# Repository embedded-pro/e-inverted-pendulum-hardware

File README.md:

# e-inverted-pendulum — Hardware

Hardware for the [e-inverted-pendulum](https://github.com/embedded-pro/e-inverted-pendulum) two-wheeled self-balancing
robot. The PCB is the robot's chassis: one vertical 85 × 130 mm 4-layer board carries the electronics, the battery and
the motor bracket. Built and assembled at JLCPCB.

This repository holds the **KiCad** design, the Python scripts that generate the schematic and sync the board, and the
ngspice simulation suite. The firmware lives in its own repository and is the source of the requirements.

> **Status: Phase 3 (layout), placement handed to the owner (D-032).** Phases 0–2 (requirements, schematic,
> simulation) are signed off. The schematic is complete, simulated and ERC-clean; the board has its outline, rule
> areas and bracket holes, with every part in the staging area. See [docs/plan.md](docs/plan.md) for the phase gates.

---

## Highlights

- **STM32WB55RGV6** with BLE 5. The whole RF corner is a copy of ST's NUCLEO-WB55 (MB1355 rev D-01, D-037): internal
  SMPS, 32 MHz HSE without external caps, `MLPF-WB55-01E3` → 3.6 nH / 1.2 pF match → printed meander antenna on
  ST's ground-free tab at the top-left corner (PCB antenna only, D-038). The MCU decoupling sits on top at the
  Nucleo's spots, or the nearest free spot to each pin (DS11929 Fig. 16 values, D-038).
- **DRV8711 gate driver with four external half-bridges** (`CSD88537ND`) for two MG310 gear motors: indexer bypassed
  (PWMMODE 1), 50 mΩ low-side shunts with Kelvin taps, 2.0 A trip, SS34 clamps on every phase node. The power stage is
  a copy of TI's BOOST-DRV8711 (D-040, `docs/drive.md`).
- **Battery path:** XT30, 4 A fuse, back-to-back `AO4805` P-FETs for reverse polarity and switching, with a simulated
  Miller soft start; `SMBJ15A` after the FETs.
- **Rails:** `TPS62933F` buck to 5 V (encoders, RGB LEDs, LDO), `TLV75533P` LDO to 3.3 V, ferrite-filtered VDDA.
- **12 RGB LEDs** (`WS2812B-2020-V6`) on one PA7 timer/DMA pin through a 5 V `SN74AHCT1G125`: it is also a toy (D-035).
  No buttons, no buzzer.
- **Test pads** on every sheet (rails, motor phases and shunts, PWM, SPI, encoders, IMU, I2C), net names on the silk.
- **Sensors and storage:** `MPU-6500` IMU on SPI2, `W25Q16JV` flash on SPI1, `M24C64` EEPROM and an `M24SR64-Y` NFC tag
  with a printed 13.56 MHz coil on I2C3, plus a Qwiic port.
- **Encoder inputs:** ESD at the connector, 100 Ω + 1 nF, `SN74LVC3G17` Schmitt buffers with 5 V-tolerant inputs.

---

## Board architecture

The schematic has 8 hierarchical sheets, one functional block each, drawn as titled boxes with design notes (the
e-psu-hardware pattern, D-033):

| Sheet | Function | Key parts |
|-------|----------|-----------|
| `e-inverted-pendulum.kicad_sch` | Root: sheet descriptions, power flow, grounding | — |
| `power_entry` | Battery input, fuse, power switch with soft start, TVS, VBAT sense | `AO4805`, `SMBJ15A`, XT30 |
| `logic_power` | 5V0 buck and 3V3 LDO | `TPS62933F`, `TLV75533P` |
| `mcu` | MCU pin map, decoupling, SMPS, clocks, reset/boot, STDC14 debug | `STM32WB55RGV6` |
| `rf` | 2.4 GHz path and printed antenna | `MLPF-WB55-01E3` |
| `drive` | Gate driver, four half-bridges, current sense | `DRV8711`, `CSD88537ND` |
| `motors_encoders` | Motor + encoder connectors, encoder conditioning | JST PH 6-pin, `TPD4E05U06`, `SN74LVC3G17` |
| `imu_flash` | IMU and SPI flash | `MPU-6500`, `W25Q16JV` |
| `ui` | Status LED, 12 RGB LEDs, Qwiic, EEPROM, NFC tag | `WS2812B-2020-V6`, `SN74AHCT1G125`, `M24C64`, `M24SR64-Y` |

---

## Design requirements

The firmware is the requirement source. [docs/requirements.md](docs/requirements.md) traces every hardware
requirement to a firmware `REQ-*` ID or to a decision in [docs/decisions.md](docs/decisions.md). The key targets:

| Item | Target | Source |
|------|--------|--------|
| Battery | 3S LiPo, 9.0–12.6 V, XT30, reverse-polarity protected | D-011, D-021 |
| Motors | 2 × MG310 1:20 (7.4 V), average motor voltage capped at 7.4 V by firmware | D-027 |
| Drive | DRV8711, PWMMODE 1, trip 2.0 A (ISGAIN 20, TORQUE 186), 0.5 A continuous by firmware I²t | D-027, S0 |
| Encoders | Hall A/B, no index; 1040 counts per wheel revolution (13 PPR is an assumption) | D-028 |
| Radio | BLE on the STM32WB55, RF corner copied from ST's NUCLEO-WB55 (MB1355) | D-001, D-007, D-037 |
| PCB | 85 × 130 mm, 4 layers JLC04161H-7628, L2 solid GND, JLCPCB assembly | D-008, D-024 |

[docs/firmware-interface.md](docs/firmware-interface.md) lists the settings the firmware must apply (DRV8711 registers,
voltage cap, ADC scaling, clock trims, I2C addresses).

### Simulation

`python3 simulation/run_all.py` runs S0–S5 (motor sizing, power entry, H-bridge switching, bus ripple, rails, ADC and
encoder edges). Two power-entry failures and one phase-node abs-max violation were found and fixed in the schematic.
Details: [simulation/REPORT.md](simulation/REPORT.md).

---

## Repository layout

```
e-inverted-pendulum-hardware/
├── hardware/
│   └── e-inverted-pendulum/          # KiCad 10 project
│       ├── e-inverted-pendulum.kicad_pro / .kicad_sch (root) / .kicad_pcb / .kicad_dru
│       ├── power_entry / logic_power / mcu / rf / drive / motors_encoders / imu_flash / ui .kicad_sch
│       ├── e-inverted-pendulum.kicad_sym    # project symbols
│       ├── e-inverted-pendulum.pretty/      # project footprints (XT30, STDC14, MB1355_* and MB1163_* from ST, ...)
│       └── sym-lib-table, fp-lib-table
├── scripts/
│   ├── schgen/                       # schematic generator: design/*.py -> hardware/ (D-020, D-033)
│   ├── pcb/                          # board sync (add-only, D-032), RF / NFC corner pastes (rf_block.py D-037, nfc_block.py D-039), renders
│   ├── export_review.py              # review package     -> review_exports/<board>/
│   ├── export_jlcpcb.py              # fab + assembly     -> manufacturing/<board>/
│   ├── export_release.py             # release bundle     -> release/<board>-<version>.zip
│   ├── visual_diff.py                # PR visual diff     -> diff/<board>/
│   ├── rf_reference.py               # ST MB1355 files (reference/, gitignored) -> pcb/mb1355_rf.json + MB1355_* footprints
│   ├── nfc_reference.py              # ST MB1163 Gerbers (reference/, gitignored) -> pcb/mb1163_nfc.json + MB1163_* footprints
│   └── check_*.py, design_calcs.py, nfc_coil.py, gcpw.py, export_bom.py, jlc_stock.py
├── simulation/                       # ngspice suite (S0–S5) + REPORT.md
├── pin-data/                         # pin map and the DS11929 package data it is checked against
├── bom/                              # part catalogue, BOM, stock check
├── docs/
│   ├── plan.md, requirements.md, decisions.md, design-calcs.md, power-map.md, rf.md, nfc.md, layout.md, ...
│   ├── robot-hardware-design-guide.md    # design and review knowledge base
│   ├── schematic.pdf
│   └── images/                       # board renders
├── .claude/agents/pendulum-board-reviewer.md   # design-review agent
├── PROJECT_CONTEXT.md                # design summary, decisions, open items
└── .github/workflows/                # hardware checks, kicad-bot, visual diff, release
```

Generated outputs are gitignored: `review_exports/`, `manufacturing/`, `release/`, `diff/`.

---

## Getting started

KiCad 10 project. Open `hardware/e-inverted-pendulum/e-inverted-pendulum.kicad_pro`.

```bash
git clone https://github.com/embedded-pro/e-inverted-pendulum-hardware.git
```

### Headless checks (the same ones CI runs)

```bash
python3 scripts/check_pinmap.py --firmware ../e-inverted-pendulum
```

```bash
python3 scripts/schgen/build.py
```

```bash
python3 scripts/schgen/check.py
```

```bash
kicad-cli sch erc --severity-all --exit-code-violations hardware/e-inverted-pendulum/e-inverted-pendulum.kicad_sch
```

```bash
python3 scripts/check_netlist.py && python3 scripts/check_library.py
```

### Changing the schematic

The schematic is generated: edit `scripts/schgen/design/<sheet>.py`, then rebuild. `scripts/schgen/render.sh` rebuilds,
checks the netlist against `expected.json`, writes `docs/schematic.pdf` and renders each sheet to PNG. After a
drawing-only change, prove the circuit is unchanged against the last commit:

```bash
python3 scripts/schgen/check_equivalence.py HEAD
```

Then bring the board in line (new parts land in the staging area; nothing on the board moves):

```bash
python3 scripts/pcb/board.py --rules <path to pcb_rules.py from the pcb-design-rules skill>
```

The RF corner is a copy of ST's NUCLEO-WB55 (MB1355 rev D-01, D-037). It is pasted once, and a second
run does nothing (since D-046 it is no longer a group and has no pours; `docs/rf.md`):

```bash
python3 scripts/pcb/rf_block.py --apply
```

`scripts/rf_reference.py` re-derives `scripts/pcb/mb1355_rf.json` and the `MB1355_*` footprints from ST's files, which are
kept out of the repository in `reference/mb1355/` (ST's Open Platform License).

The NFC corner is a copy of ST's X-NUCLEO-NFC01A1 (MB1163 rev C-01, D-039): the M24SR64-Y, its ANT14 coil, tuning caps,
copper and pour, pasted the same way (`docs/nfc.md`). `scripts/nfc_reference.py` re-derives `scripts/pcb/mb1163_nfc.json`
and the `MB1163_*` footprints from ST's Gerbers in `reference/mb1163/`; `scripts/nfc_coil.py` checks the coil.

```bash
python3 scripts/pcb/nfc_block.py --apply
```

### Review and fabrication packages

- The export, BOM, stock, datasheet and visual-diff scripts are thin wrappers around the hardware-design plugin's,
  pinned in `scripts/plugin.py`; `python3 scripts/plugin_gates.py` runs the plugin's gates as CI does (D-064).
- `python3 scripts/export_review.py`: ERC/DRC, netlist, BOM, PDFs and renders for a design review, used by the
  `pendulum-board-reviewer` agent in [`.claude/agents/`](.claude/agents/).
- `python3 scripts/export_jlcpcb.py`: Gerbers, drill, BOM and CPL for JLCPCB.
- `python3 scripts/export_bom.py` then `python3 scripts/jlc_stock.py bom/bom.csv --boards 5`: BOM and live stock.

---

## Before ordering

1. Finish Phase 3: placement (owner), routing, DRC clean with schematic parity, the `power-pcb-layout` §7 and
   `rf-layout` §12 checklists ([docs/plan.md](docs/plan.md)).
2. Re-run the stock check; every line must be in stock for the order quantity.
3. JLCPCB options (PCB + assembly, D-036): 4 layers, JLC04161H-7628, 1.6 mm, 1 oz outer / 0.5 oz inner; impedance
   control only if JLCPCB holds MB1355's RF line as drawn (0.6 / 0.2 mm on L1 over L3, `docs/rf.md`). Check every CPL rotation in the preview
   (the WS2812B-2020 footprint is the datasheet pattern turned 180°).
4. Leave the DNP parts off: antenna-match C401, shield clips SC401–SC404, NFC tuning spares C821–C823 and pull-ups R805 / R806, sense filters C501/C504, motor
   snubbers C603/C607, encoder pull-ups, R602.

---

## Continuous integration

- [`hardware.yml`](.github/workflows/hardware.yml): pin map, regenerate the schematic with no diff, netlist against
  the generator's intent, ERC, netlist and symbol/footprint checks.
- [`kicad-bot.yml`](.github/workflows/kicad-bot.yml): [kicad-bot](https://github.com/embedded-pro/kicad-bot) ERC/DRC
  with schematic parity, on pushes to `main` and on pull requests; DRC does not fail the build until the board is
  routed. kicad-bot runs without KiCad's libraries, so its ERC shows library-lookup warnings; `hardware.yml` is the
  library check.
- [`kicad-diff.yml`](.github/workflows/kicad-diff.yml): red/green visual diff of schematic and board on pull requests.
- KiCad on GitHub runners: `scripts/install_kicad.sh 10` (and kicad-bot ≥ v0.1.5) pins the KiCad PPA to `amd64`.
  Ubuntu 26.04 runners otherwise install Ubuntu's KiCad 9, which can't open this project; the script fails if
  `kicad-cli` isn't 10.x.
- [`release.yml`](.github/workflows/release.yml): [release-please](https://github.com/googleapis/release-please) from
  Conventional Commits; each release attaches the fabrication bundle from `scripts/export_release.py`.

Third-party actions are pinned to a full commit SHA. CI is a guardrail, not a design review: use the
`pendulum-board-reviewer` agent with [docs/robot-hardware-design-guide.md](docs/robot-hardware-design-guide.md) for that.

Design rules come from the `hardware-design` skills in
[claude-hardware-skills](https://github.com/gabrielfrasantos/claude-hardware-skills).

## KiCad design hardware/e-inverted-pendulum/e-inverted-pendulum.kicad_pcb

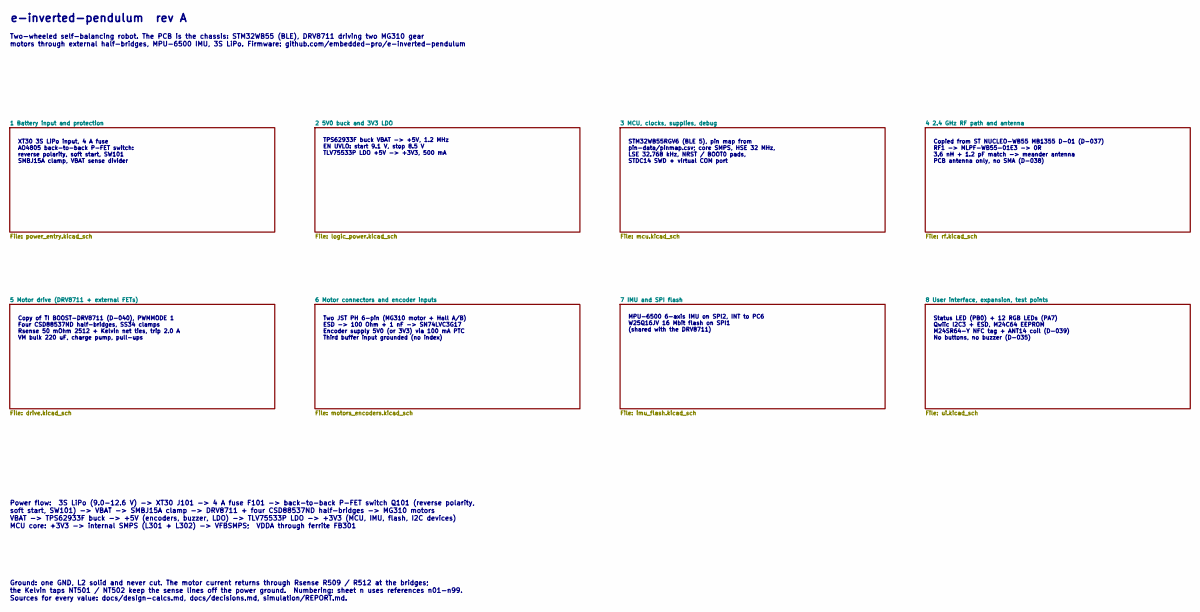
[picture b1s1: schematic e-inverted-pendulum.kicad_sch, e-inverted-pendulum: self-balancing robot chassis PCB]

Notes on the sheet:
Two JST PH 6-pin (MG310 motor + Hall A/B) ESD -> 100 Ohm + 1 nF -> SN74LVC3G17 Encoder supply 5V0 (or 3V3) via 100 mA PTC Third buffer input grounded (no index)
Copy of TI BOOST-DRV8711 (D-040), PWMMODE 1 Four CSD88537ND half-bridges, SS34 clamps Rsense 50 mOhm 2512 + Kelvin net ties, trip 2.0 A VM bulk 220 uF, charge pump, pull-ups
Copied from ST NUCLEO-WB55 MB1355 D-01 (D-037) RF1 -> MLPF-WB55-01E3 -> 0R 3.6 nH + 1.2 pF match -> meander antenna PCB antenna only, no SMA (D-038)
MPU-6500 6-axis IMU on SPI2, INT to PC6 W25Q16JV 16 Mbit flash on SPI1 (shared with the DRV8711)
Status LED (PB0) + 12 RGB LEDs (PA7) Qwiic I2C3 + ESD, M24C64 EEPROM M24SR64-Y NFC tag + ANT14 coil (D-039) No buttons, no buzzer (D-035)
Two-wheeled self-balancing robot. The PCB is the chassis: STM32WB55 (BLE), DRV8711 driving two MG310 gear motors through external half-bridges, MPU-6500 IMU, 3S LiPo. Firmware: github.com/embedded-pro/e-inverted-pendulum
XT30 3S LiPo input, 4 A fuse AO4805 back-to-back P-FET switch: reverse polarity, soft start, SW101 SMBJ15A clamp, VBAT sense divider
e-inverted-pendulum rev A
TPS62933F buck VBAT -> +5V, 1.2 MHz EN UVLO: start 9.1 V, stop 8.5 V TLV75533P LDO +5V -> +3V3, 500 mA
Ground: one GND, L2 solid and never cut. The motor current returns through Rsense R509 / R512 at the bridges; the Kelvin taps NT501 / NT502 keep the sense lines off the power ground. Numbering: sheet n uses references n01-n99. Sources for every value: docs/design-calcs.md, docs/decisions.md, simula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
STM32WB55RGV6 (BLE 5), pin map from pin-data/pinmap.csv; core SMPS, HSE 32 MHz, LSE 32.768 kHz, NRST / BOOT0 pads, STDC14 SWD + virtual COM port
Power flow: 3S LiPo (9.0-12.6 V) -> XT30 J101 -> 4 A fuse F101 -> back-to-back P-FET switch Q101 (reverse polarity, soft start, SW101) -> VBAT -> SMBJ15A clamp -> DRV8711 + four CSD88537ND half-bridges -> MG310 motors VBAT -> TPS62933F buck -> +5V (encoders, buzzer, LDO) -> TLV75533P LDO -> +3V3 (M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

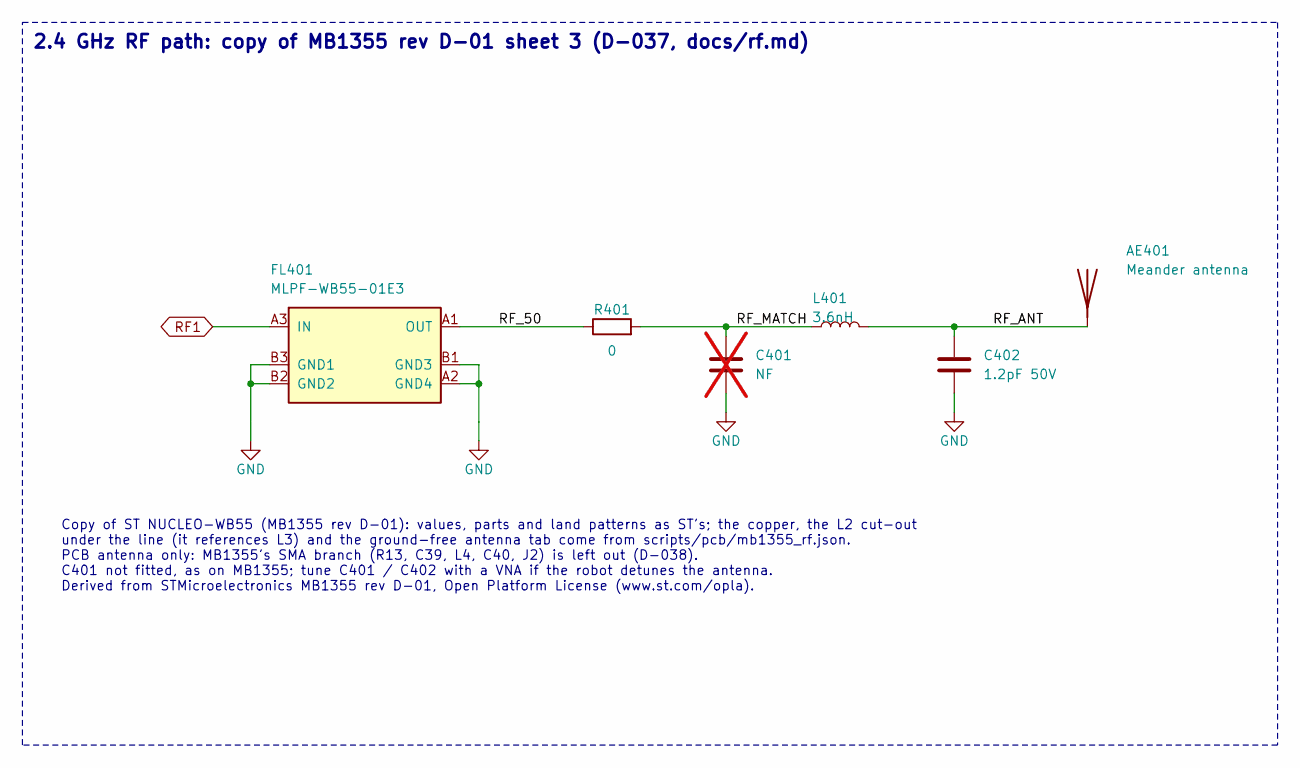
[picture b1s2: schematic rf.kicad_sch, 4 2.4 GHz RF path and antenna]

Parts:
AE401: Meander antenna; MB1355_Meander_Antenna
C401: NF; MB1355_0402_CAP_NPOL; not fitted
C402: 1.2pF 50V; MB1355_0402_CAP_NPOL; MPN GJM1555C1H1R2WB01D; LCSC C76899
FL401: MLPF-WB55-01E3; MB1355_ST_CSP650x58P2x3_160x100x42; MPN MLPF-WB55-01E3; LCSC C2651048
L401: 3.6nH; MB1355_0402_COIL; MPN LQG15HS3N6S02D; LCSC C19216
R401: 0; MB1355_0402_RES; MPN 0402WGF0000TCE; LCSC C17168

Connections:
/4 2.4 GHz RF path and antenna/RF_50: FL401.A1 (OUT), R401.1
/4 2.4 GHz RF path and antenna/RF_ANT: AE401.1, C402.1, L401.2
/4 2.4 GHz RF path and antenna/RF_MATCH: C401.1, L401.1, R401.2
GND: C401.2, C402.2, FL401.A2 (GND4), FL401.B1 (GND3), FL401.B2 (GND2), FL401.B3 (GND1); also elsewhere on the board
RF1: FL401.A3 (IN); also elsewhere on the board

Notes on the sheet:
2.4 GHz RF path: copy of MB1355 rev D-01 sheet 3 (D-037, docs/rf.md)
Copy of ST NUCLEO-WB55 (MB1355 rev D-01): values, parts and land patterns as ST's; the copper, the L2 cut-out under the line (it references L3) and the ground-free antenna tab come from scripts/pcb/mb1355_rf.json. PCB antenna only: MB1355's SMA branch (R13, C39, L4, C40, J2) is left out (D-038). C4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

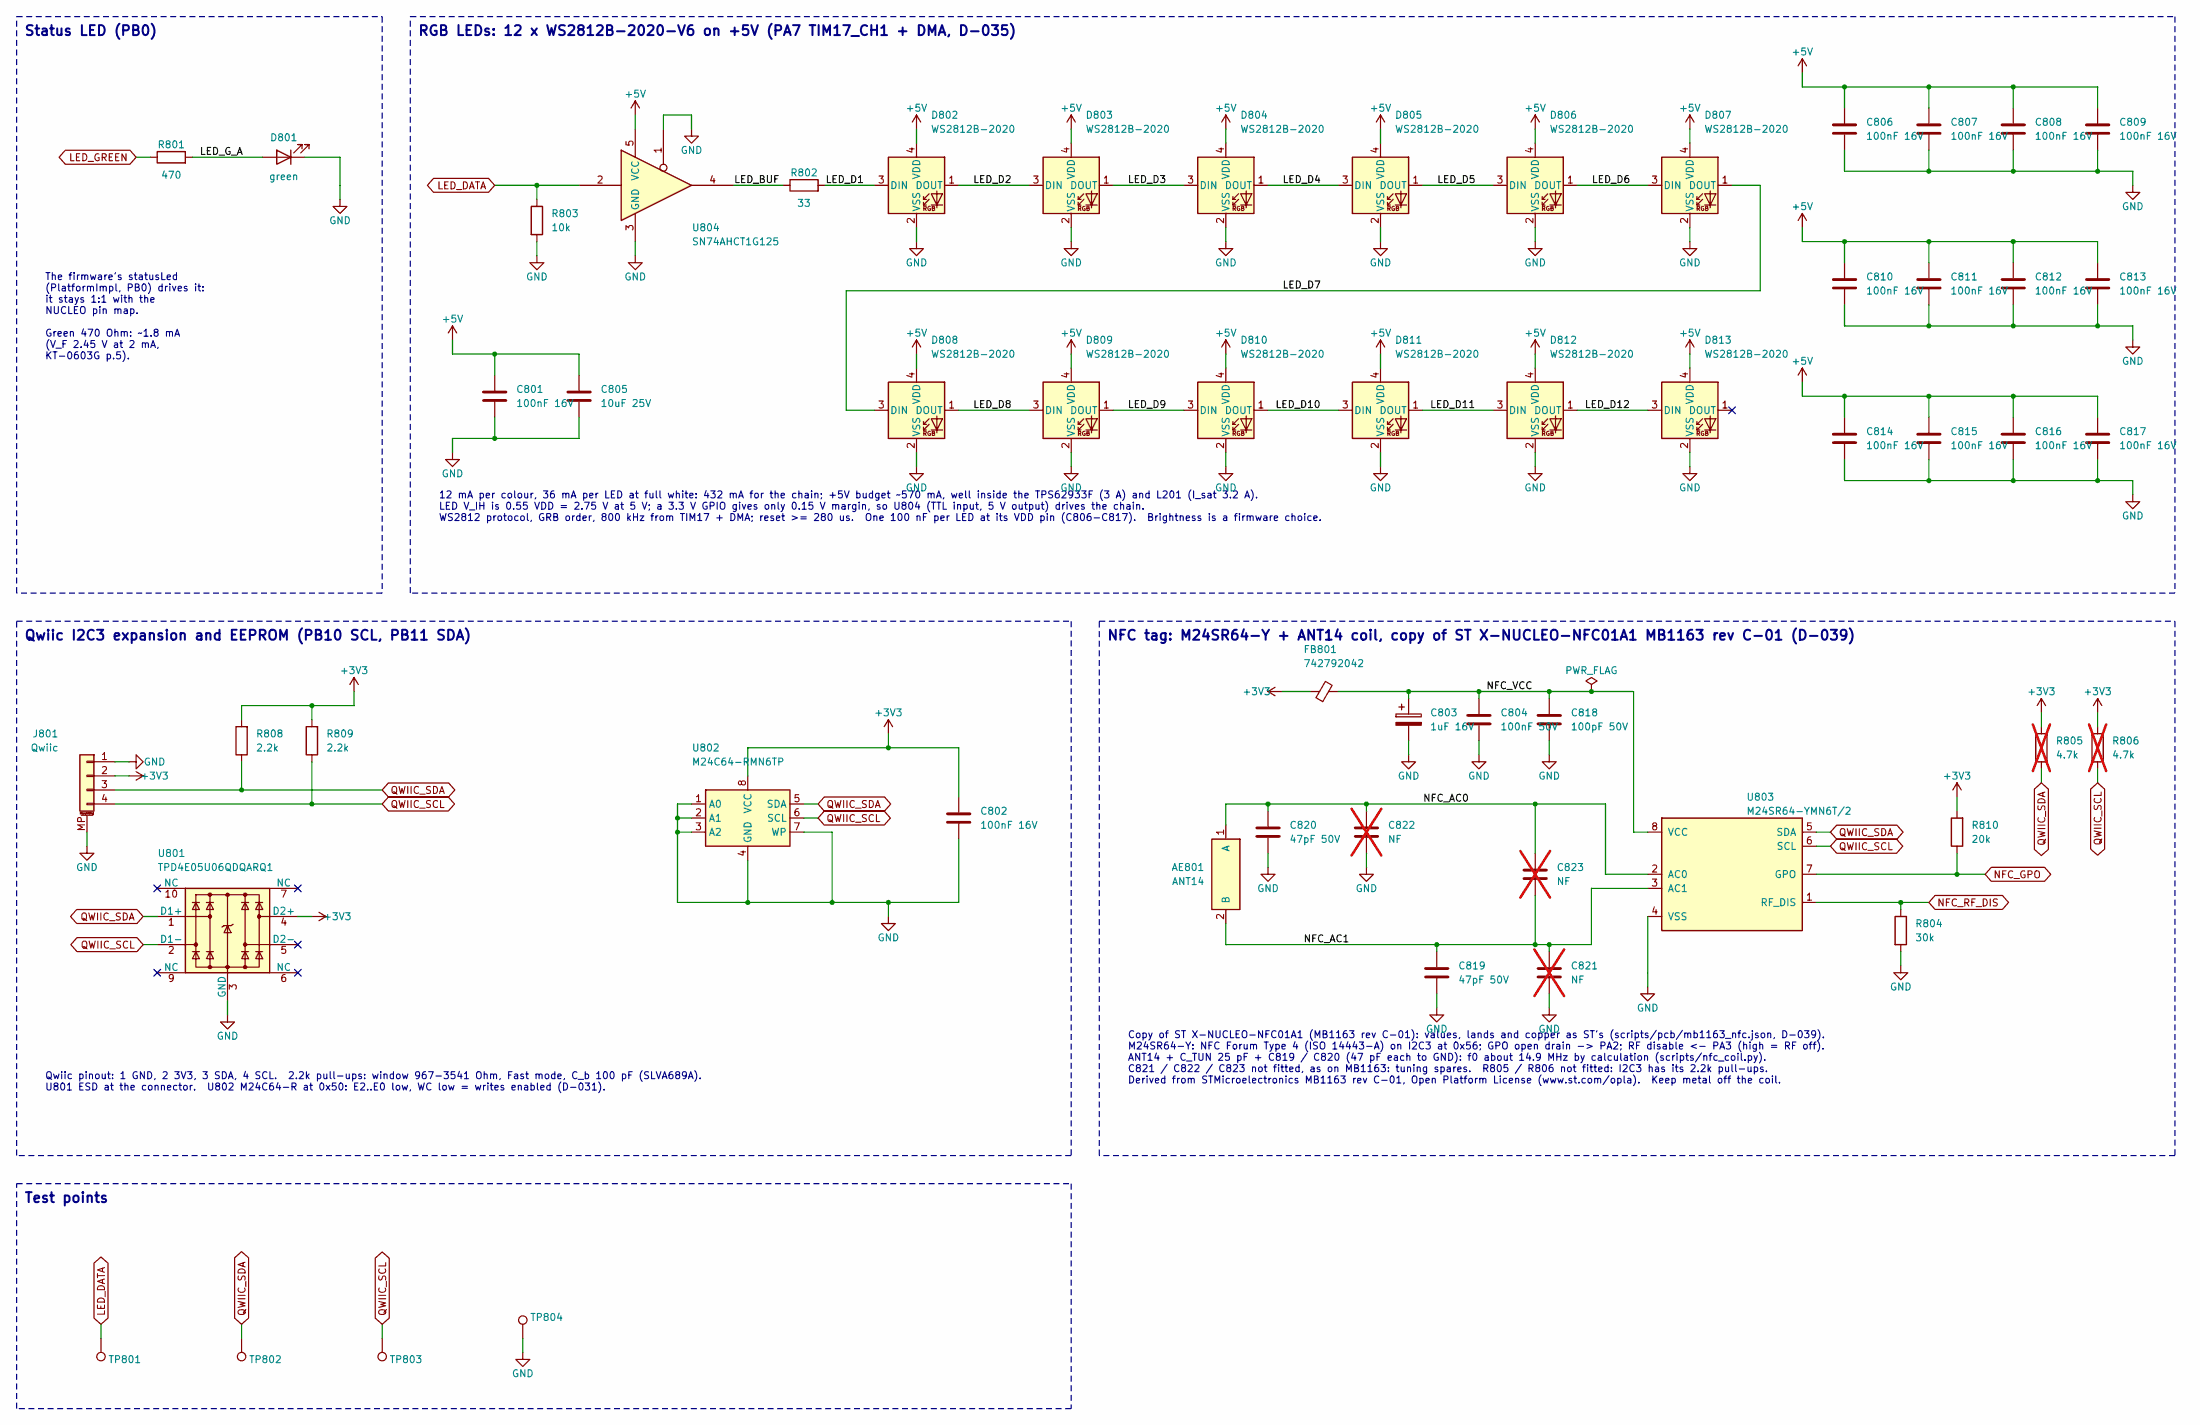
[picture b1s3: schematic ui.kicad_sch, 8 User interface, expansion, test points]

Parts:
AE801: ANT14; MB1163_ANT14
C801, C802, C806, C807, C808, C809, C810, C811, C812, C813, C814, C815, C816, C817: 100nF 16V; C_0402_1005Metric; MPN CL05B104KO5NNNC; LCSC C1525
C803: 1uF 16V; MB1163_CP_293D_A; MPN 293D105X9016A2TE3; LCSC C162327
C804: 100nF 50V; MB1163_C_0603; MPN CC0603KRX7R9BB104; LCSC C14663
C805: 10uF 25V; C_0805_2012Metric; MPN CL21A106KAYNNNE; LCSC C15850
C818: 100pF 50V; MB1163_C_0603; MPN CL10C101JB8NNNC; LCSC C14858
C819, C820: 47pF 50V; MB1163_C_0603; MPN CL10C470JB8NNNC; LCSC C1671
C821, C822, C823: NF; MB1163_C_0603; not fitted
D801: green; LED_0603_1608Metric; MPN KT-0603G; LCSC C12624
D802, D803, D804, D805, D806, D807, D808, D809, D810, D811, D812, D813: WS2812B-2020; LED_WS2812B-2020_PLCC4_2.0x2.0mm; MPN WS2812B-2020-V6; LCSC C52917434
FB801: 742792042; MB1163_L_0805; MPN 742792042; LCSC C5374796
J801: Qwiic; JST_SH_SM04B-SRSS-TB_1x04-1MP_P1.00mm_Horizontal; MPN SM04B-SRSS-TB(LF)(SN); LCSC C160404
R801: 470; R_0603_1608Metric; MPN 0603WAF4700T5E; LCSC C23179
R802: 33; R_0603_1608Metric; MPN 0603WAF330JT5E; LCSC C23140
R803: 10k; R_0603_1608Metric; MPN 0603WAF1002T5E; LCSC C25804
R804: 30k; MB1163_R_0603; MPN 0603WAF3002T5E; LCSC C22984
R805, R806: 4.7k; MB1163_R_0603; MPN 0603WAF4701T5E; LCSC C23162; not fitted
R808, R809: 2.2k; R_0603_1608Metric; MPN 0603WAF2201T5E; LCSC C4190
R810: 20k; MB1163_R_0603; MPN 0603WAF2002T5E; LCSC C4184
TP801: LED_DATA; TestPoint_Pad_D1.0mm
TP802: QWIIC_SDA; TestPoint_Pad_D1.0mm
TP803: QWIIC_SCL; TestPoint_Pad_D1.0mm
TP804: GND; TestPoint_Pad_D1.5mm
U801: TPD4E05U06QDQARQ1; USON-10_2.5x1.0mm_P0.5mm; MPN TPD4E05U06QDQARQ1; LCSC C81353
U802: M24C64-RMN6TP; SOIC-8_3.9x4.9mm_P1.27mm; MPN M24C64-RMN6TP; LCSC C79988
U803: M24SR64-YMN6T/2; MB1163_SO8; MPN M24SR64-YMN6T/2; LCSC C222221
U804: SN74AHCT1G125; SOT-23-5; MPN SN74AHCT1G125DBVR; LCSC C7484

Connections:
+3V3: C802.1, FB801.1, J801.2, R805.2, R806.2, R808.2, R809.2, R810.2, U801.4 (D2+), U802.8 (VCC); also elsewhere on the board
+5V: C801.1, C805.1, C806.1, C807.1, C808.1, C809.1, C810.1, C811.1, C812.1, C813.1, C814.1, C815.1, C816.1, C817.1, D802.4 (VDD), D803.4 (VDD), D804.4 (VDD), D805.4 (VDD), D806.4 (VDD), D807.4 (VDD), D808.4 (VDD), D809.4 (VDD), D810.4 (VDD), D811.4 (VDD), D812.4 (VDD), D813.4 (VDD), U804.5 (VCC); also elsewhere on the board
/8 User interface, expansion, test points/LED_BUF: R802.1, U804.4
/8 User interface, expansion, test points/LED_D1: D802.3 (DIN), R802.2
/8 User interface, expansion, test points/LED_D2: D802.1 (DOUT), D803.3 (DIN)
/8 User interface, expansion, test points/LED_D3: D803.1 (DOUT), D804.3 (DIN)
/8 User interface, expansion, test points/LED_D4: D804.1 (DOUT), D805.3 (DIN)
/8 User interface, expansion, test points/LED_D5: D805.1 (DOUT), D806.3 (DIN)
/8 User interface, expansion, test points/LED_D6: D806.1 (DOUT), D807.3 (DIN)
/8 User interface, expansion, test points/LED_D7: D807.1 (DOUT), D808.3 (DIN)
/8 User interface, expansion, test points/LED_D8: D808.1 (DOUT), D809.3 (DIN)
/8 User interface, expansion, test points/LED_D9: D809.1 (DOUT), D810.3 (DIN)
/8 User interface, expansion, test points/LED_D10: D810.1 (DOUT), D811.3 (DIN)
/8 User interface, expansion, test points/LED_D11: D811.1 (DOUT), D812.3 (DIN)
/8 User interface, expansion, test points/LED_D12: D812.1 (DOUT), D813.3 (DIN)
/8 User interface, expansion, test points/LED_G_A: D801.2 (A), R801.2
/8 User interface, expansion, test points/NFC_AC0: AE801.1 (A), C820.1, C822.1, C823.1, U803.2 (AC0)
/8 User interface, expansion, test points/NFC_AC1: AE801.2 (B), C819.1, C821.1, C823.2, U803.3 (AC1)
/8 User interface, expansion, test points/NFC_VCC: C803.1, C804.1, C818.1, FB801.2, U803.8 (VCC)
GND: C801.2, C802.2, C803.2, C804.2, C805.2, C806.2, C807.2, C808.2, C809.2, C810.2, C811.2, C812.2, C813.2, C814.2, C815.2, C816.2, C817.2, C818.2, C819.2, C820.2, C821.2, C822.2, D801.1 (K), D802.2 (VSS), D803.2 (VSS), D804.2 (VSS), D805.2 (VSS), D806.2 (VSS), D807.2 (VSS), D808.2 (VSS), D809.2 (VSS), D810.2 (VSS), D811.2 (VSS), D812.2 (VSS), D813.2 (VSS), J801.1, J801.MP (MountPin), R803.2, R804.2, TP804.1, U801.3 (GND), U801.8 (GND), U802.1 (A0), U802.2 (A1), U802.3 (A2), U802.4 (GND), U802.7 (WP), U803.4 (VSS), U804.1, U804.3 (GND); also elsewhere on the board
LED_DATA: R803.1, TP801.1, U804.2; also elsewhere on the board
LED_GREEN: R801.1; also elsewhere on the board
NFC_GPO: R810.1, U803.7 (GPO); also elsewhere on the board
NFC_RF_DIS: R804.1, U803.1 (RF_DIS); also elsewhere on the board
QWIIC_SCL: J801.4, R806.1, R809.1, TP803.1, U801.2 (D1-), U802.6 (SCL), U803.6 (SCL); also elsewhere on the board
QWIIC_SDA: J801.3, R805.1, R808.1, TP802.1, U801.1 (D1+), U802.5 (SDA), U803.5 (SDA); also elsewhere on the board

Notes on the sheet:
Copy of ST X-NUCLEO-NFC01A1 (MB1163 rev C-01): values, lands and copper as ST's (scripts/pcb/mb1163_nfc.json, D-039). M24SR64-Y: NFC Forum Type 4 (ISO 14443-A) on I2C3 at 0x56; GPO open drain -> PA2; RF disable <- PA3 (high = RF off). ANT14 + C_TUN 25 pF + C819 / C820 (47 pF each to GND): f0 about 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
Qwiic I2C3 expansion and EEPROM (PB10 SCL, PB11 SDA)
Qwiic pinout: 1 GND, 2 3V3, 3 SDA, 4 SCL. 2.2k pull-ups: window 967-3541 Ohm, Fast mode, C_b 100 pF (SLVA689A). U801 ESD at the connector. U802 M24C64-R at 0x50: E2..E0 low, WC low = writes enabled (D-031).
Test points
Status LED (PB0)
NFC tag: M24SR64-Y + ANT14 coil, copy of ST X-NUCLEO-NFC01A1 MB1163 rev C-01 (D-039)
12 mA per colour, 36 mA per LED at full white: 432 mA for the chain; +5V budget ~570 mA, well inside the TPS62933F (3 A) and L201 (I_sat 3.2 A). LED V_IH is 0.55 VDD = 2.75 V at 5 V; a 3.3 V GPIO gives only 0.15 V margin, so U804 (TTL input, 5 V output) drives the chain. WS2812 protocol, GRB order,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
The firmware's statusLed (PlatformImpl, PB0) drives it: it stays 1:1 with the NUCLEO pin map. Green 470 Ohm: ~1.8 mA (V_F 2.45 V at 2 mA, KT-0603G p.5).
RGB LEDs: 12 x WS2812B-2020-V6 on +5V (PA7 TIM17_CH1 + DMA, D-035)

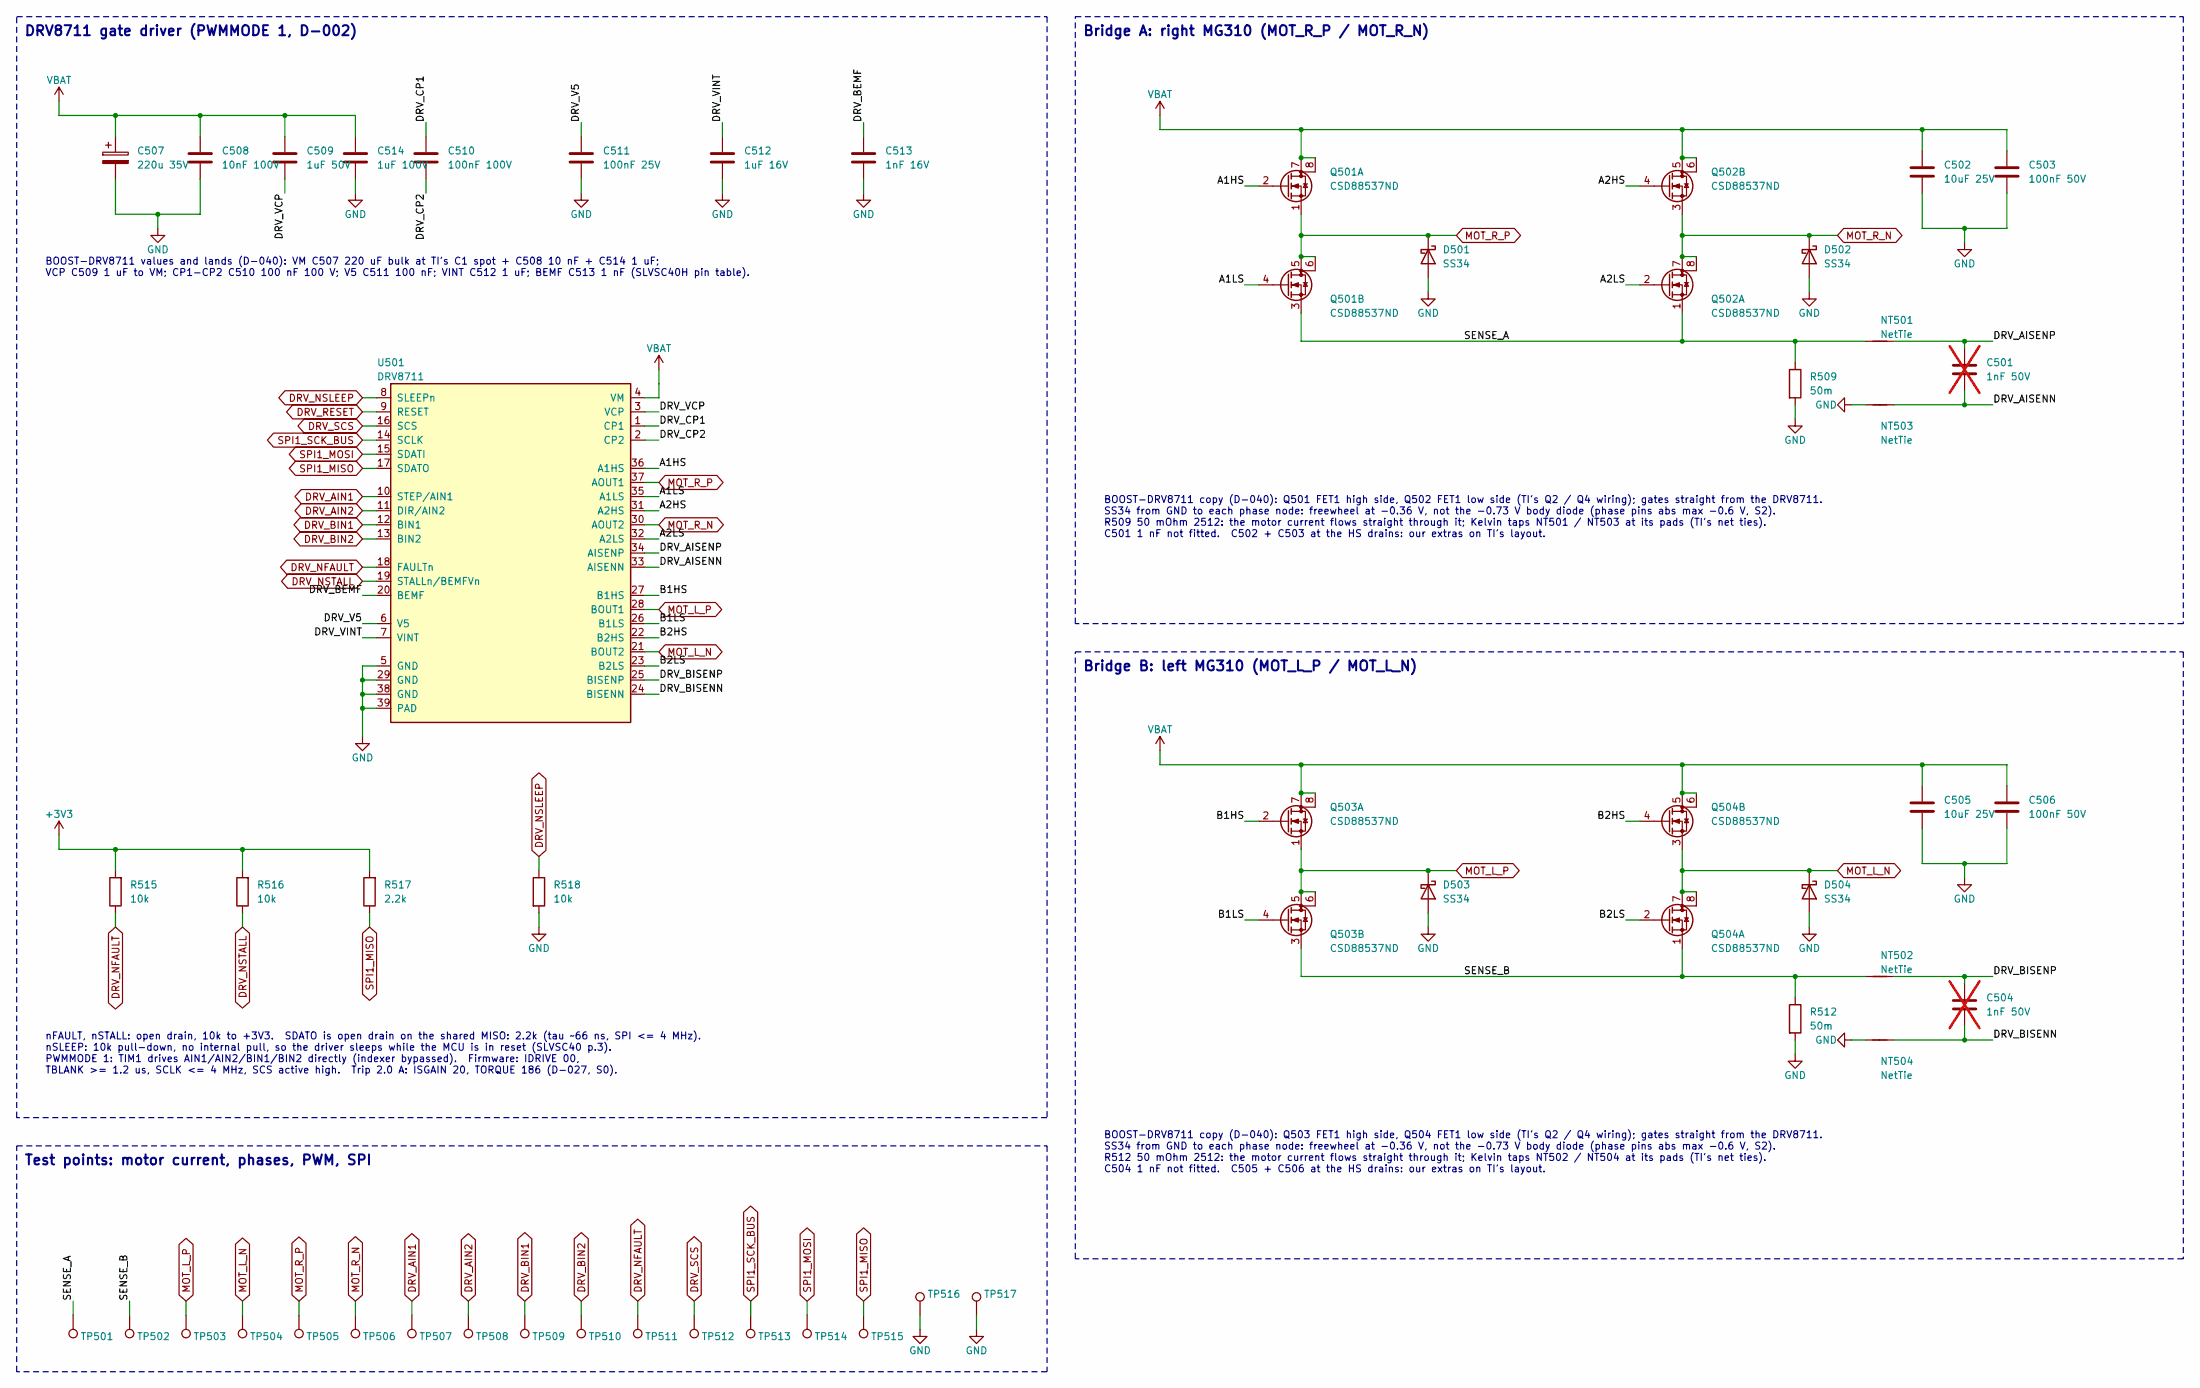
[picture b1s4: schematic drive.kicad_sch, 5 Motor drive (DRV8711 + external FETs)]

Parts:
C501, C504: 1nF 50V; C_0402_1005Metric; MPN CL05C102JB5NNNC; LCSC C307441; not fitted
C502, C505: 10uF 25V; C_0805_2012Metric; MPN CL21A106KAYNNNE; LCSC C15850
C503, C506: 100nF 50V; C_0603_1608Metric; MPN CC0603KRX7R9BB104; LCSC C14663
C507: 220u 35V; CP_Elec_8x10; MPN EEEFK1V221P; LCSC C178562
C508: 10nF 100V; BOOST_0603L; MPN C1608X7R2A103KT000N; LCSC C342523
C509: 1uF 50V; BOOST_0805L; MPN CL21B105KBFNNNE; LCSC C28323
C510: 100nF 100V; BOOST_0603L; MPN GRM188R72A104KA35D; LCSC C77058
C511: 100nF 25V; BOOST_0603L; MPN C1608X7R1E104KT000N; LCSC C338036
C512: 1uF 16V; BOOST_0603L; MPN C1608X7R1C105KT000N; LCSC C76617
C513: 1nF 16V; BOOST_0603L; MPN C0603C102K4RACTU; LCSC C22402015
C514: 1uF 100V; BOOST_1206L; MPN CL31B105KCHNNNE; LCSC C13832
D501, D502, D503, D504: SS34; D_SMA; MPN SS34; LCSC C8678
NT501, NT502, NT503, NT504: NetTie; BOOST_Net-Tie_10mil
Q501, Q502, Q503, Q504: CSD88537ND; BOOST_SO-8; MPN CSD88537ND; LCSC C117439
R509, R512: 50m; BOOST_2512M; MPN CRA2512-FZ-R050ELF; LCSC C840617
R515, R516, R518: 10k; R_0603_1608Metric; MPN 0603WAF1002T5E; LCSC C25804
R517: 2.2k; R_0603_1608Metric; MPN 0603WAF2201T5E; LCSC C4190
TP501: SENSE_A; TestPoint_Pad_D1.0mm
TP502: SENSE_B; TestPoint_Pad_D1.0mm
TP503: MOT_L_P; TestPoint_Pad_D1.0mm
TP504: MOT_L_N; TestPoint_Pad_D1.0mm
TP505: MOT_R_P; TestPoint_Pad_D1.0mm
TP506: MOT_R_N; TestPoint_Pad_D1.0mm
TP507: DRV_AIN1; TestPoint_Pad_D1.0mm
TP508: DRV_AIN2; TestPoint_Pad_D1.0mm
TP509: DRV_BIN1; TestPoint_Pad_D1.0mm
TP510: DRV_BIN2; TestPoint_Pad_D1.0mm
TP511: DRV_NFAULT; TestPoint_Pad_D1.0mm
TP512: DRV_SCS; TestPoint_Pad_D1.0mm
TP513: SPI1_SCK_BUS; TestPoint_Pad_D1.0mm
TP514: SPI1_MOSI; TestPoint_Pad_D1.0mm
TP515: SPI1_MISO; TestPoint_Pad_D1.0mm
TP516, TP517: GND; TestPoint_Pad_D1.5mm
U501: DRV8711; BOOST_R-PDSO-G38; MPN DRV8711DCPR; LCSC C60013

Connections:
+3V3: R515.2, R516.2, R517.2; also elsewhere on the board
/5 Motor drive (DRV8711 + external FETs)/A1HS: Q501.2 (G), U501.36 (A1HS)
/5 Motor drive (DRV8711 + external FETs)/A1LS: Q501.4 (G), U501.35 (A1LS)
/5 Motor drive (DRV8711 + external FETs)/A2HS: Q502.4 (G), U501.31 (A2HS)
/5 Motor drive (DRV8711 + external FETs)/A2LS: Q502.2 (G), U501.32 (A2LS)
/5 Motor drive (DRV8711 + external FETs)/B1HS: Q503.2 (G), U501.27 (B1HS)
/5 Motor drive (DRV8711 + external FETs)/B1LS: Q503.4 (G), U501.26 (B1LS)
/5 Motor drive (DRV8711 + external FETs)/B2HS: Q504.4 (G), U501.22 (B2HS)
/5 Motor drive (DRV8711 + external FETs)/B2LS: Q504.2 (G), U501.23 (B2LS)
/5 Motor drive (DRV8711 + external FETs)/DRV_AISENN: C501.2, NT503.1, U501.33 (AISENN)
/5 Motor drive (DRV8711 + external FETs)/DRV_AISENP: C501.1, NT501.1, U501.34 (AISENP)
/5 Motor drive (DRV8711 + external FETs)/DRV_BEMF: C513.1, U501.20 (BEMF)
/5 Motor drive (DRV8711 + external FETs)/DRV_BISENN: C504.2, NT504.1, U501.24 (BISENN)
/5 Motor drive (DRV8711 + external FETs)/DRV_BISENP: C504.1, NT502.1, U501.25 (BISENP)
/5 Motor drive (DRV8711 + external FETs)/DRV_CP1: C510.1, U501.1 (CP1)
/5 Motor drive (DRV8711 + external FETs)/DRV_CP2: C510.2, U501.2 (CP2)
/5 Motor drive (DRV8711 + external FETs)/DRV_V5: C511.1, U501.6 (V5)
/5 Motor drive (DRV8711 + external FETs)/DRV_VCP: C509.1, U501.3 (VCP)
/5 Motor drive (DRV8711 + external FETs)/DRV_VINT: C512.1, U501.7 (VINT)
/5 Motor drive (DRV8711 + external FETs)/SENSE_A: NT501.2, Q501.3 (S), Q502.1 (S), R509.1, TP501.1
/5 Motor drive (DRV8711 + external FETs)/SENSE_B: NT502.2, Q503.3 (S), Q504.1 (S), R512.1, TP502.1
DRV_AIN1: TP507.1, U501.10 (STEP/AIN1); also elsewhere on the board
DRV_AIN2: TP508.1, U501.11 (DIR/AIN2); also elsewhere on the board
DRV_BIN1: TP509.1, U501.12 (BIN1); also elsewhere on the board
DRV_BIN2: TP510.1, U501.13 (BIN2); also elsewhere on the board
DRV_NFAULT: R515.1, TP511.1, U501.18 (FAULTn); also elsewhere on the board
DRV_NSLEEP: R518.1, U501.8 (SLEEPn); also elsewhere on the board
DRV_NSTALL: R516.1, U501.19 (STALLn/BEMFVn); also elsewhere on the board
DRV_RESET: U501.9 (RESET); also elsewhere on the board
DRV_SCS: TP512.1, U501.16 (SCS); also elsewhere on the board
GND: C502.2, C503.2, C505.2, C506.2, C507.2, C508.2, C511.2, C512.2, C513.2, C514.2, D501.2 (A), D502.2 (A), D503.2 (A), D504.2 (A), NT503.2, NT504.2, R509.2, R512.2, R518.2, TP516.1, TP517.1, U501.5 (GND), U501.29 (GND), U501.38 (GND), U501.39 (PAD); also elsewhere on the board
MOT_L_N: D504.1 (K), Q504.3 (S), Q504.7 (D), Q504.8 (D), TP504.1, U501.21 (BOUT2); also elsewhere on the board
MOT_L_P: D503.1 (K), Q503.1 (S), Q503.5 (D), Q503.6 (D), TP503.1, U501.28 (BOUT1); also elsewhere on the board
MOT_R_N: D502.1 (K), Q502.3 (S), Q502.7 (D), Q502.8 (D), TP506.1, U501.30 (AOUT2); also elsewhere on the board
MOT_R_P: D501.1 (K), Q501.1 (S), Q501.5 (D), Q501.6 (D), TP505.1, U501.37 (AOUT1); also elsewhere on the board
SPI1_MISO: R517.1, TP515.1, U501.17 (SDATO); also elsewhere on the board
SPI1_MOSI: TP514.1, U501.15 (SDATI); also elsewhere on the board
SPI1_SCK_BUS: TP513.1, U501.14 (SCLK); also elsewhere on the board
VBAT: C502.1, C503.1, C505.1, C506.1, C507.1, C508.1, C509.2, C514.1, Q501.7 (D), Q501.8 (D), Q502.5 (D), Q502.6 (D), Q503.7 (D), Q503.8 (D), Q504.5 (D), Q504.6 (D), U501.4 (VM); also elsewhere on the board

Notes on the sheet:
Test points: motor current, phases, PWM, SPI
Bridge B: left MG310 (MOT_L_P / MOT_L_N)
Bridge A: right MG310 (MOT_R_P / MOT_R_N)
BOOST-DRV8711 copy (D-040): Q503 FET1 high side, Q504 FET1 low side (TI's Q2 / Q4 wiring); gates straight from the DRV8711. SS34 from GND to each phase node: freewheel at -0.36 V, not the -0.73 V body diode (phase pins abs max -0.6 V, S2). R512 50 mOhm 2512: the motor current flows straight through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
nFAULT, nSTALL: open drain, 10k to +3V3. SDATO is open drain on the shared MISO: 2.2k (tau ~66 ns, SPI <= 4 MHz). nSLEEP: 10k pull-down, no internal pull, so the driver sleeps while the MCU is in reset (SLVSC40 p.3). PWMMODE 1: TIM1 drives AIN1/AIN2/BIN1/BIN2 directly (indexer bypassed). Firmware: 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
BOOST-DRV8711 copy (D-040): Q501 FET1 high side, Q502 FET1 low side (TI's Q2 / Q4 wiring); gates straight from the DRV8711. SS34 from GND to each phase node: freewheel at -0.36 V, not the -0.73 V body diode (phase pins abs max -0.6 V, S2). R509 50 mOhm 2512: the motor current flows straight through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
DRV8711 gate driver (PWMMODE 1, D-002)
BOOST-DRV8711 values and lands (D-040): VM C507 220 uF bulk at TI's C1 spot + C508 10 nF + C514 1 uF; VCP C509 1 uF to VM; CP1-CP2 C510 100 nF 100 V; V5 C511 100 nF; VINT C512 1 uF; BEMF C513 1 nF (SLVSC40H pin table).
